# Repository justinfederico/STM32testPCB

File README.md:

# STM32testPCB
Custom STM32WB microcontroller to practice my PCB schematic and layout skills. Looking to get it printed soon! Bear in mind that this is an ameuter project, so there will probably be errors aplenty. Feel free to let me know about them.

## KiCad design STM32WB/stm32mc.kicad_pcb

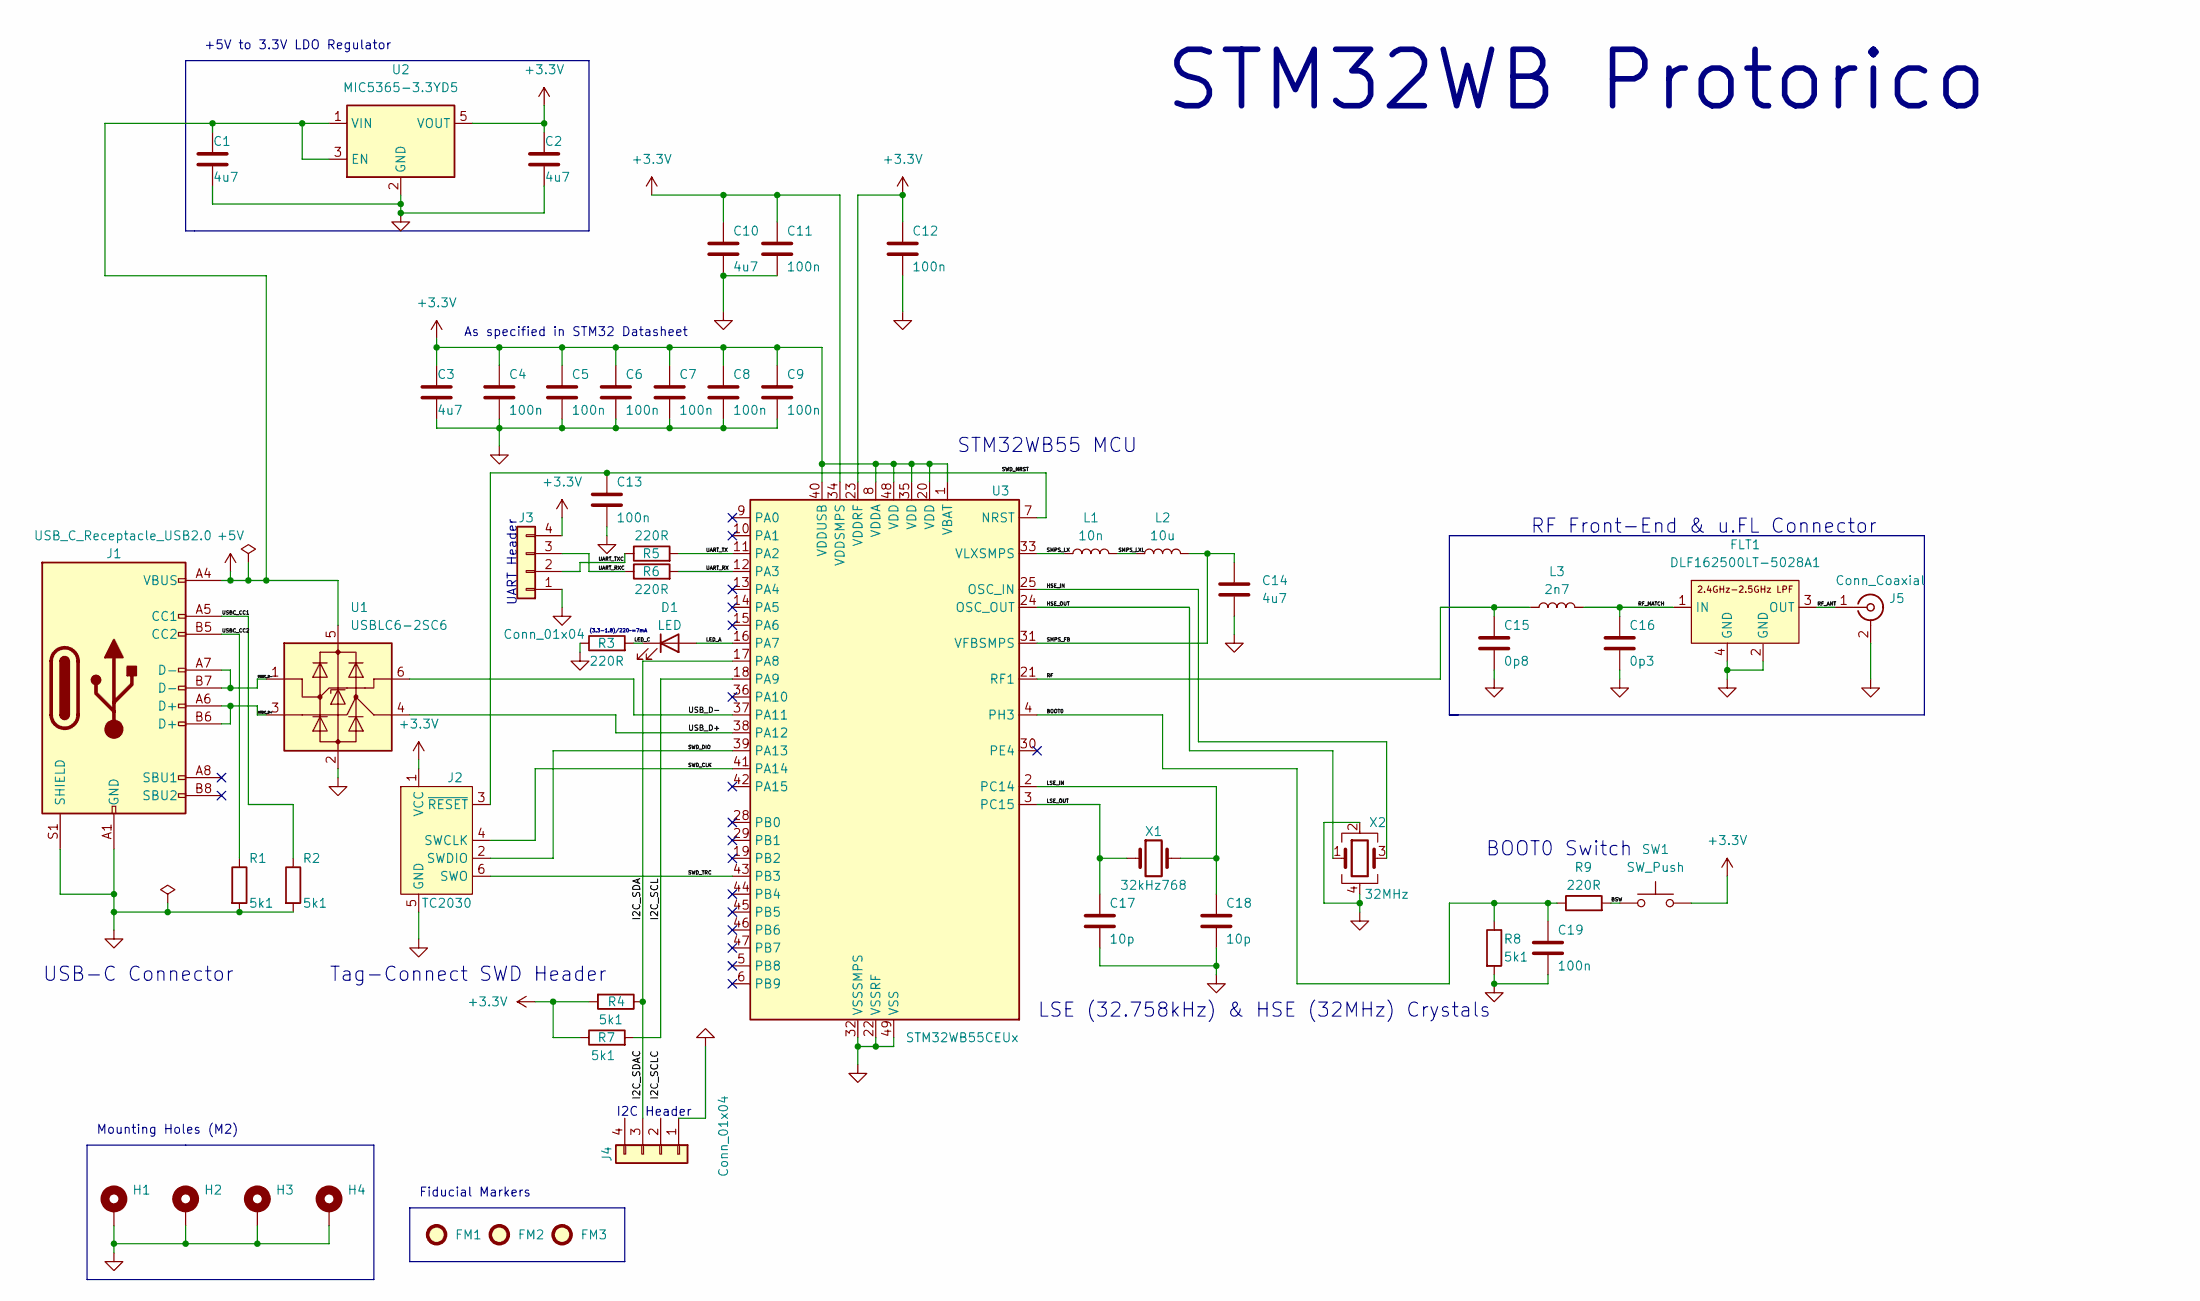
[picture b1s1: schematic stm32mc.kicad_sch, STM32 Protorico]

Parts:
C1, C2, C3, C10, C14: 4u7; C_0603_1608Metric; Manufacturer Part Number 0603YD475MAT2A
C4, C5, C6, C7, C8, C9, C11, C12, C13, C19: 100n; C_0402_1005Metric; Manufacturer Part Number 04023C104KAT2A
C15: 0p8; C_0402_1005Metric; Manufacturer Part Number GRM1555C1HR80BA01D
C16: 0p3; C_0402_1005Metric; Manufacturer Part Number GRM1555C1HR30WA01D
C17, C18: 10p; C_0402_1005Metric; Manufacturer Part Number 04025A100JAT4A
D1: LED; LED_0402_1005Metric; Manufacturer Part Number 150040RS73240
FLT1: DLF162500LT-5028A1; Manufacturer Part Number DLF162500LT-5028A1
FM1, FM2, FM3: Fiducial; Fiducial_1mm_Mask2mm
H1, H2, H3, H4: MountingHole_Pad; MountingHole_2.2mm_M2_Pad_Via
J1: USB_C_Receptacle_USB2.0; USB_C_Receptacle_GCT_USB4105-xx-A_16P_TopMnt_Horizontal; Manufacturer Part Number USB4105-GF-A
J2: TC2030; Tag-Connect_TC2030-IDC-FP_2x03_P1.27mm_Vertical
J3, J4: Conn_01x04; Molex_PicoBlade_53048-0410_1x04_P1.25mm_Horizontal; Manufacturer Part Number 53048-0410
J5: Conn_Coaxial; U.FL_Hirose_U.FL-R-SMT-1_Vertical; Manufacturer Part Number U.FL-R-SMT-1(01)
L1: 10n; L_0402_1005Metric; Manufacturer Part Number LQG15WZ10NJ02D
L2: 10u; L_0805_2012Metric; Manufacturer Part Number LQM21FN100M70L
L3: 2n7; L_0402_1005Metric; Manufacturer Part Number LQG15HS2N7S02D
R1, R2, R4, R7, R8: 5k1; R_0402_1005Metric; Manufacturer Part Number RC0603FR-075K1L
R3, R5, R6, R9: 220R; R_0402_1005Metric; Manufacturer Part Number RC0402FR-07221RL
SW1: SW_Push; SW_SPST_CK_RS282G05A3; Manufacturer Part Number RS282G05A3SMRT
U1: USBLC6-2SC6; SOT-23-6; Manufacturer Part Number USBLC6-2SC6
U2: MIC5365-3.3YD5; SOT-23-5; Manufacturer Part Number MIC5365-3.3YD5-TR
U3: STM32WB55CEUx; QFN-48-1EP_7x7mm_P0.5mm_EP5.6x5.6mm; Manufacturer Part Number STM32WB55CEU6
X1: 32kHz768; Crystal_SMD_2012-2Pin_2.0x1.2mm; Manufacturer Part Number NX2012SA-32.768K-STD-MUB-1
X2: 32MHz; Crystal_SMD_2016-4Pin_2.0x1.6mm; Manufacturer Part Number NX2016SA-32M-EXS00A-CS06465

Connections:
+3.3V: C2.1, C3.1, C4.1, C5.1, C6.1, C7.1, C8.1, C9.1, C10.1, C11.1, C12.1, J2.1 (VCC), J3.4, J4.4, R4.2, R7.1, SW1.2, U2.5 (VOUT), U3.1 (VBAT), U3.8 (VDDA), U3.20 (VDD), U3.23 (VDDRF), U3.34 (VDDSMPS), U3.35 (VDD), U3.40 (VDDUSB), U3.48 (VDD)
+5V: C1.1, J1.A4 (VBUS), J1.A9 (VBUS), J1.B4 (VBUS), J1.B9 (VBUS), U1.5 (VBUS), U2.1 (VIN), U2.3 (EN)
/BOOT0: C19.1, R8.1, R9.1, U3.4 (PH3)
/BSW: R9.2, SW1.1
/HSE_IN: U3.25 (OSC_IN), X2.3
/HSE_OUT: U3.24 (OSC_OUT), X2.1
/I2C_SCL: J4.2, R7.2, U3.18 (PA9)
/I2C_SDA: J4.3, R4.1, U3.17 (PA8)
/LED_A: D1.2 (A), U3.16 (PA7)
/LED_C: D1.1 (K), R3.2
/LSE_IN: C18.1, U3.2 (PC14), X1.2
/LSE_OUT: C17.1, U3.3 (PC15), X1.1
/RF: C15.1, L3.1, U3.21 (RF1)
/RF_ANT: FLT1.3 (OUT), J5.1 (In)
/RF_MATCH: C16.1, FLT1.1 (IN), L3.2
/SMPS_FB: C14.1, L2.2, U3.31 (VFBSMPS)
/SMPS_LX: L1.1, U3.33 (VLXSMPS)
/SMPS_LXL: L1.2, L2.1
/SWD_CLK: J2.4 (SWCLK), U3.41 (PA14)
/SWD_DIO: J2.2 (SWDIO), U3.39 (PA13)
/SWD_NRST: C13.1, J2.3 (~RESET), U3.7 (NRST)
/SWD_TRC: J2.6 (SWO), U3.43 (PB3)
/UART_RX: R6.2, U3.12 (PA3)
/UART_RXC: J3.3, R6.1
/UART_TX: R5.2, U3.11 (PA2)
/UART_TXC: J3.2, R5.1
/USBC_CC1: J1.A5 (CC1), R2.1
/USBC_CC2: J1.B5 (CC2), R1.1
/USBC_D+: J1.A6 (D+), J1.B6 (D+), U1.3 (I/O2)
/USBC_D-: J1.A7 (D-), J1.B7 (D-), U1.1 (I/O1)
/USB_D+: U1.4 (I/O2), U3.38 (PA12)
/USB_D-: U1.6 (I/O1), U3.37 (PA11)
GND: C1.2, C2.2, C3.2, C4.2, C5.2, C6.2, C7.2, C8.2, C9.2, C10.2, C11.2, C12.2, C13.2, C14.2, C15.2, C16.2, C17.2, C18.2, C19.2, FLT1.2 (GND), FLT1.4 (GND), H1.1, H2.1, H3.1, H4.1, J1.A1 (GND), J1.A12 (GND), J1.B1 (GND), J1.B12 (GND), J1.S1 (SHIELD), J2.5 (GND), J3.1, J4.1, J5.2 (Ext), R1.2, R2.2, R3.1, R8.2, U1.2 (GND), U2.2 (GND), U3.22 (VSSRF), U3.32 (VSSSMPS), U3.49 (VSS), X2.2, X2.4

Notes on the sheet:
As specified in STM32 Datasheet
USB-C Connector
Fiducial Markers
BOOT0 Switch
STM32WB55 MCU
I2C Header
+5V to 3.3V LDO Regulator
Mounting Holes (M2)
UART Header
STM32WB Protorico
RF Front-End & u.FL Connector
(3.3-1.8)/220~=7mA
LSE (32.758kHz) & HSE (32MHz) Crystals
Tag-Connect SWD Header

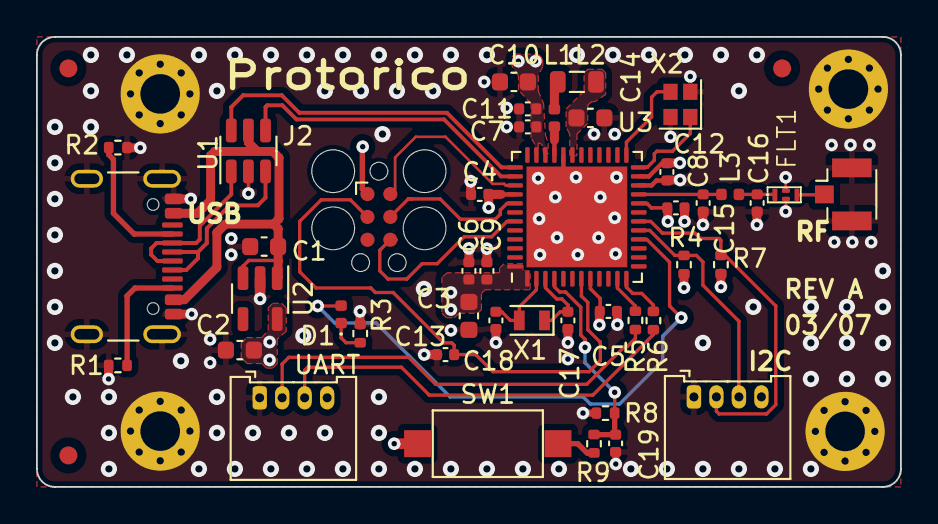
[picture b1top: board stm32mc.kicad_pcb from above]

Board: 4 copper layers, 48.0 x 25.0 mm, 51 parts (0 on the bottom side), 33 nets.

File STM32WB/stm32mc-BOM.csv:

"Source:","C:\Users\justi\Documents\Hardware Projects\stm32mc\stm32mc.kicad_sch"
"Date:","3/7/2024 9:46:58 PM"
"Tool:","Eeschema 7.0.9"
"Generator:","C:\Program Files\KiCad\7.0\bin\scripting\plugins/bom_csv_custom.py"
"Component Count:","43"
"Ref","Qnty","Value","Footprint","Description","Manufacturer","Manufacturer Part Number","Distributor Link"
"C1, C2, C3, C10, C14","5","4u7","Capacitor_SMD:C_0603_1608Metric","Unpolarized capacitor","KYOCERA AVX","0603YD475MAT2A","",""
"C4, C5, C6, C7, C8, C9, C11, C12, C13, C19","10","100n","Capacitor_SMD:C_0402_1005Metric","Unpolarized capacitor","KYOCERA AVX","04023C104KAT2A","",""
"C15","1","0p8","Capacitor_SMD:C_0402_1005Metric","Unpolarized capacitor","Murata Electronics","GRM1555C1HR80BA01D","",""
"C16","1","0p3","Capacitor_SMD:C_0402_1005Metric","Unpolarized capacitor","Murata Electronics","GRM1555C1HR30WA01D","",""
"C17, C18","2","10p","Capacitor_SMD:C_0402_1005Metric","Unpolarized capacitor","KYOCERA AVX","04025A100JAT4A","",""
"D1","1","LED","LED_SMD:LED_0402_1005Metric","Light emitting diode","Wurth","150040RS73240","",""
"FLT1","1","DLF162500LT-5028A1","STM_MCU:DLF162500LT-5028A1","","TDK","DLF162500LT-5028A1","",""
"J1","1","USB_C_Receptacle_USB2.0","Connector_USB:USB_C_Receptacle_GCT_USB4105-xx-A_16P_TopMnt_Horizontal","USB 2.0-only Type-C Receptacle connector","GCT","USB4105-GF-A","",""
"J3, J4","2","Conn_01x04","Connector_Molex:Molex_PicoBlade_53048-0410_1x04_P1.25mm_Horizontal","Generic connector, single row, 01x04, script generated (kicad-library-utils/schlib/autogen/connector/)","Molex","53048-0410","",""
"J5","1","Conn_Coaxial","Connector_Coaxial:U.FL_Hirose_U.FL-R-SMT-1_Vertical","coaxial connector (BNC, SMA, SMB, SMC, Cinch/RCA, LEMO, ...)","Hirose","U.FL-R-SMT-1(01)","",""
"L1","1","10n","Inductor_SMD:L_0402_1005Metric","Inductor","Murata","LQG15WZ10NJ02D","",""
"L2","1","10u","Inductor_SMD:L_0805_2012Metric","Inductor","Murata","LQM21FN100M70L","",""
"L3","1","2n7","Inductor_SMD:L_0402_1005Metric","Inductor","Murata","LQG15HS2N7S02D","",""
"R1, R2, R4, R7, R8","5","5k1","Resistor_SMD:R_0402_1005Metric","Resistor","YAGEO","RC0603FR-075K1L","",""
"R3, R5, R6, R9","4","220R","Resistor_SMD:R_0402_1005Metric","Resistor","YAGEO","RC0402FR-07221RL","",""
"SW1","1","SW_Push","Button_Switch_SMD:SW_SPST_CK_RS282G05A3","Push button switch, generic, two pins","C&K","RS282G05A3SMRT","",""
"U1","1","USBLC6-2SC6","Package_TO_SOT_SMD:SOT-23-6","Very low capacitance ESD protection diode, 2 data-line, SOT-23-6","STMicroelectronics","USBLC6-2SC6","",""
"U2","1","MIC5365-3.3YD5","Package_TO_SOT_SMD:SOT-23-5","150mA Low-dropout Voltage Regulator, Vout 3.3V, Vin up to 5.5V, SOT-23-5","Microchip","MIC5365-3.3YD5-TR","",""
"U3","1","STM32WB55CEUx","Package_DFN_QFN:QFN-48-1EP_7x7mm_P0.5mm_EP5.6x5.6mm","STMicroelectronics Arm Cortex-M4 MCU, 512KB flash, 256KB RAM, 64 MHz, 1.71-3.6V, 30 GPIO, UFQFPN48","STMicroelectronics","STM32WB55CEU6","",""
"X1","1","32kHz768","Crystal:Crystal_SMD_2012-2Pin_2.0x1.2mm","Two pin crystal","NDK","NX2012SA-32.768K-STD-MUB-1 ","",""
"X2","1","32MHz","Crystal:Crystal_SMD_2016-4Pin_2.0x1.6mm","Four pin crystal, GND on pins 2 and 4","NDK","NX2016SA-32M-EXS00A-CS06465","",""

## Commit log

2024-04-15 Add files via upload
    ZIP of all the files relevant to the project. Will be updated and organized when I improve the functionality and layout scheme.
2024-04-15 Makin a folder lol
2024-04-15 Relevant footprints, files, schematics, and all that
2024-04-15 Files to manufacture the board at a PCB maker like PCBway
2024-04-15 Add files via upload
    RF component
2024-04-15 Update README.md
    An extra period?
